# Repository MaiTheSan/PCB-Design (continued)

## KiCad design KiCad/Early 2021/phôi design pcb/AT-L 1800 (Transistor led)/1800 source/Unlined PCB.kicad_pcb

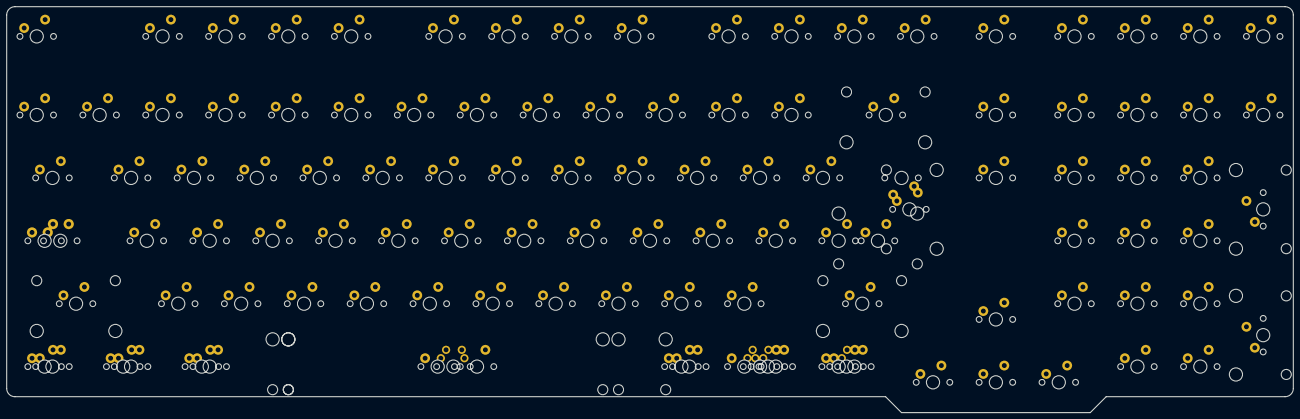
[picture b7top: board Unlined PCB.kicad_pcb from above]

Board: 2 copper layers, 389.7 x 123.0 mm, 115 parts (0 on the bottom side), 29 nets, no tracks yet.

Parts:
MX_1, MX_2, MX_3, MX_4, MX_5, MX_6, MX_7, MX_8, MX_9, MX_10: 1U; MXOnly-1U-NoLED
MX_'1: 1U; MXOnly-1U-NoLED
MX_+1: 1U; MXOnly-1U-NoLED
MX_-1: 1U; MXOnly-1U-NoLED
MX_/?/1: 1U; MXOnly-1U-NoLED
MX_;1: 1U; MXOnly-1U-NoLED
MX_<1: 1U; MXOnly-1U-NoLED
MX_>1: 1U; MXOnly-1U-NoLED
MX_A1: 1U; MXOnly-1U-NoLED
MX_ALT1: 1,5U; MXOnly-1.25U-NoLED
MX_ALT2: 1,25U FLIPPED; MXOnly-1.25U-NoLED
MX_BkSp1: 2U FLIPPED; MXOnly-2U-NoLED
MX_CapLk1: 1,25U FLIPPED; MXOnly-1U-NoLED
MX_CapLk2: 1,75U; MXOnly-1U-NoLED
MX_D1: 1U; MXOnly-1U-NoLED
MX_Delete1: 1U; MXOnly-1U-NoLED
MX_Down1: 1U; MXOnly-1.25U-NoLED
MX_E1: 1U; MXOnly-1U-NoLED
MX_ENTER1: 2,25U FLIPPED; MXOnly-2.25U-ReversedStabilizers-NoLED
MX_ENTER2: 2x2.25U ISO enter; MXOnly-ISO
MX_ESC1: 1U FLIPPED; MXOnly-1U-NoLED
MX_F1, MX_F4, MX_F5, MX_F6, MX_F8, MX_F10, MX_F11: 1U; MXOnly-1U-NoLED
MX_F2, MX_F3, MX_F7, MX_F9, MX_F12, MX_F13: 1U FLIPPED; MXOnly-1U-NoLED
MX_FN1, MX_FN2, MX_FN3: 1U; MXOnly-1U-NoLED
MX_FN4: 1U_FLIPPED; MXOnly-1U-NoLED
MX_G1: 1U; MXOnly-1U-NoLED
MX_H1: 1U; MXOnly-1U-NoLED
MX_I1: 1U; MXOnly-1U-NoLED
MX_J1: 1U; MXOnly-1U-NoLED
MX_K1: 1U; MXOnly-1U-NoLED
MX_L1: 1U; MXOnly-1U-NoLED
MX_LControl1: 1,5U; MXOnly-1.25U-NoLED
MX_LControl2: 1,25U FLIPPED; MXOnly-1.25U-NoLED
MX_LShift1: 2,25U; MXOnly-2.25U-NoLED
MX_LWin1: 1U; MXOnly-1.25U-NoLED
MX_LWin2: 1,25U NoLed; MXOnly-1.25U-NoLED
MX_Left1: 1U; MXOnly-1.25U-NoLED
MX_O1: 1U; MXOnly-1U-NoLED
MX_P1: 1U; MXOnly-1U-NoLED
MX_PrtSc1: 1U; MXOnly-1U-NoLED
MX_Q1: 1U; MXOnly-1U-NoLED
MX_R1: 1U; MXOnly-1U-NoLED
MX_RAlt1: 1,25U; MXOnly-1.25U-NoLED
MX_RAlt2: 1,5U FLIPPED; MXOnly-1.25U-NoLED
MX_RAlt4: 1,5U; MXOnly-1.25U-NoLED
MX_RControl1: 1,25U NoLed; MXOnly-1.25U-NoLED
MX_RControl2: 1U FLIPPED; MXOnly-1.25U-NoLED
MX_RControl3: 1,5U FLIPPED; MXOnly-1.25U-NoLED
MX_RShift1: 2,75U FLIPPED; MXOnly-2.75U-NoLED
MX_RWin1: NoLed; MXOnly-1.25U-NoLED
MX_RWin2: 1,5U; MXOnly-1.25U-NoLED
MX_RWin3: 1U; MXOnly-1.25U-NoLED
MX_S1: 1U; MXOnly-1U-NoLED
MX_SpaceBar1, MX_SpaceBar2: 6,25U FLIPPED; MXOnly-6.25U-ReversedStabilizers-NoLED
MX_SpaceBar3: 7U; MXOnly-7U-ReversedStabilizers-NoLED
MX_T1: 1U; MXOnly-1U-NoLED
MX_U1: 1U; MXOnly-1U-NoLED
MX_W1: 1U; MXOnly-1U-NoLED
MX_Y1: 1U; MXOnly-1U-NoLED
MX_[1: 1U; MXOnly-1U-NoLED
MX_]1: 1U; MXOnly-1U-NoLED
MX_`~1: 1U; MXOnly-1U-NoLED
MX_b1: 1U; MXOnly-1U-NoLED
MX_c1: 1U; MXOnly-1U-NoLED
MX_insert1: 1U; MXOnly-1U-NoLED
MX_m1: 1U; MXOnly-1U-NoLED
MX_n1: 1U; MXOnly-1U-NoLED
MX_num1, MX_num2, MX_num3, MX_num4, MX_num5, MX_num6, MX_num7, MX_num8, MX_num9, MX_num10: 1U; MXOnly-1U-NoLED
MX_num*1: 1U; MXOnly-1U-NoLED
MX_num+1: 2U FLIPPED; MXOnly-2U-ReversedStabilizers-NoLED
MX_num-1: 1U; MXOnly-1U-NoLED
MX_num/1: 1U; MXOnly-1U-NoLED
MX_numDel1: 1U; MXOnly-1U-NoLED
MX_numEnter1: 2U; MXOnly-2U-ReversedStabilizers-NoLED
MX_numLk1: 1U; MXOnly-1U-NoLED
MX_right1: 1U; MXOnly-1.25U-NoLED
MX_tab1: 1,5U; MXOnly-1U-NoLED
MX_up1: 1U; MXOnly-1U-NoLED
MX_v1: 1U; MXOnly-1U-NoLED
MX_x1: 1U; MXOnly-1U-NoLED
MX_z1: 1U; MXOnly-1U-NoLED
MX_|\1: 1.5U FLIPPED; MXOnly-1.5U-NoLED
MX_|\2: 1U; MXOnly-1U-NoLED

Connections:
Col0: MX_FN1.1, MX_num+1.1, MX_num-1.1, MX_numEnter1.1
Col1: MX_FN2.1, MX_num1.1, MX_num2.1, MX_num3.1, MX_num4.1, MX_num*1.1
Col2: MX_FN3.1, MX_num5.1, MX_num6.1, MX_num7.1, MX_num/1.1, MX_numDel1.1
Col3: MX_FN4.1, MX_Left1.1, MX_num8.1, MX_num9.1, MX_num10.1, MX_numLk1.1
Col4: MX_Delete1.1, MX_Down1.1, MX_PrtSc1.1, MX_insert1.1, MX_up1.1
Col5: MX_CapLk1.1, MX_CapLk2.1, MX_ESC1.1, MX_LShift1.1, MX_`~1.1, MX_right1.1, MX_tab1.1
Col6: MX_1.1, MX_A1.1, MX_LControl1.1, MX_LControl2.1, MX_Q1.1, MX_z1.1
Col7: MX_2.1, MX_F1.1, MX_LWin1.1, MX_LWin2.1, MX_S1.1, MX_W1.1, MX_x1.1
Col8: MX_3.1, MX_ALT1.1, MX_ALT2.1, MX_D1.1, MX_E1.1, MX_F2.1, MX_c1.1
Col9: MX_4.1, MX_F3.1, MX_F4.1, MX_R1.1, MX_v1.1
Col10: MX_5.1, MX_F5.1, MX_G1.1, MX_T1.1, MX_b1.1
Col11: MX_6.1, MX_F6.1, MX_H1.1, MX_SpaceBar1.1, MX_SpaceBar2.1, MX_SpaceBar3.1, MX_Y1.1, MX_n1.1
Col12: MX_7.1, MX_F7.1, MX_J1.1, MX_U1.1, MX_m1.1
Col13: MX_8.1, MX_<1.1, MX_F8.1, MX_I1.1, MX_K1.1
Col14: MX_9.1, MX_>1.1, MX_F9.1, MX_L1.1, MX_O1.1
Col15: MX_10.1, MX_/?/1.1, MX_;1.1, MX_F10.1, MX_P1.1, MX_RAlt1.1, MX_RAlt2.1
Col16: MX_'1.1, MX_-1.1, MX_F11.1, MX_RAlt4.1, MX_RWin1.1, MX_RWin2.1, MX_RWin3.1, MX_[1.1
Col17: MX_+1.1, MX_F12.1, MX_]1.1
Col18: MX_BkSp1.1, MX_ENTER1.1, MX_ENTER2.1, MX_F13.1, MX_RControl1.1, MX_RControl2.1, MX_RControl3.1, MX_RShift1.1, MX_|\1.2, MX_|\2.1
unnamed: MX_CapLk1.2, MX_CapLk2.2
unnamed: MX_LControl1.2, MX_LControl2.2
unnamed: MX_LWin1.2, MX_LWin2.2
unnamed: MX_ALT1.2, MX_ALT2.2
unnamed: MX_SpaceBar1.2, MX_SpaceBar2.2, MX_SpaceBar3.2
unnamed: MX_RAlt1.2, MX_RAlt2.2
unnamed: MX_RAlt4.2, MX_RWin1.2, MX_RWin2.2, MX_RWin3.2
unnamed: MX_ENTER2.2, MX_|\1.1
unnamed: MX_ENTER1.2, MX_|\2.2
unnamed: MX_RControl1.2, MX_RControl2.2, MX_RControl3.2
